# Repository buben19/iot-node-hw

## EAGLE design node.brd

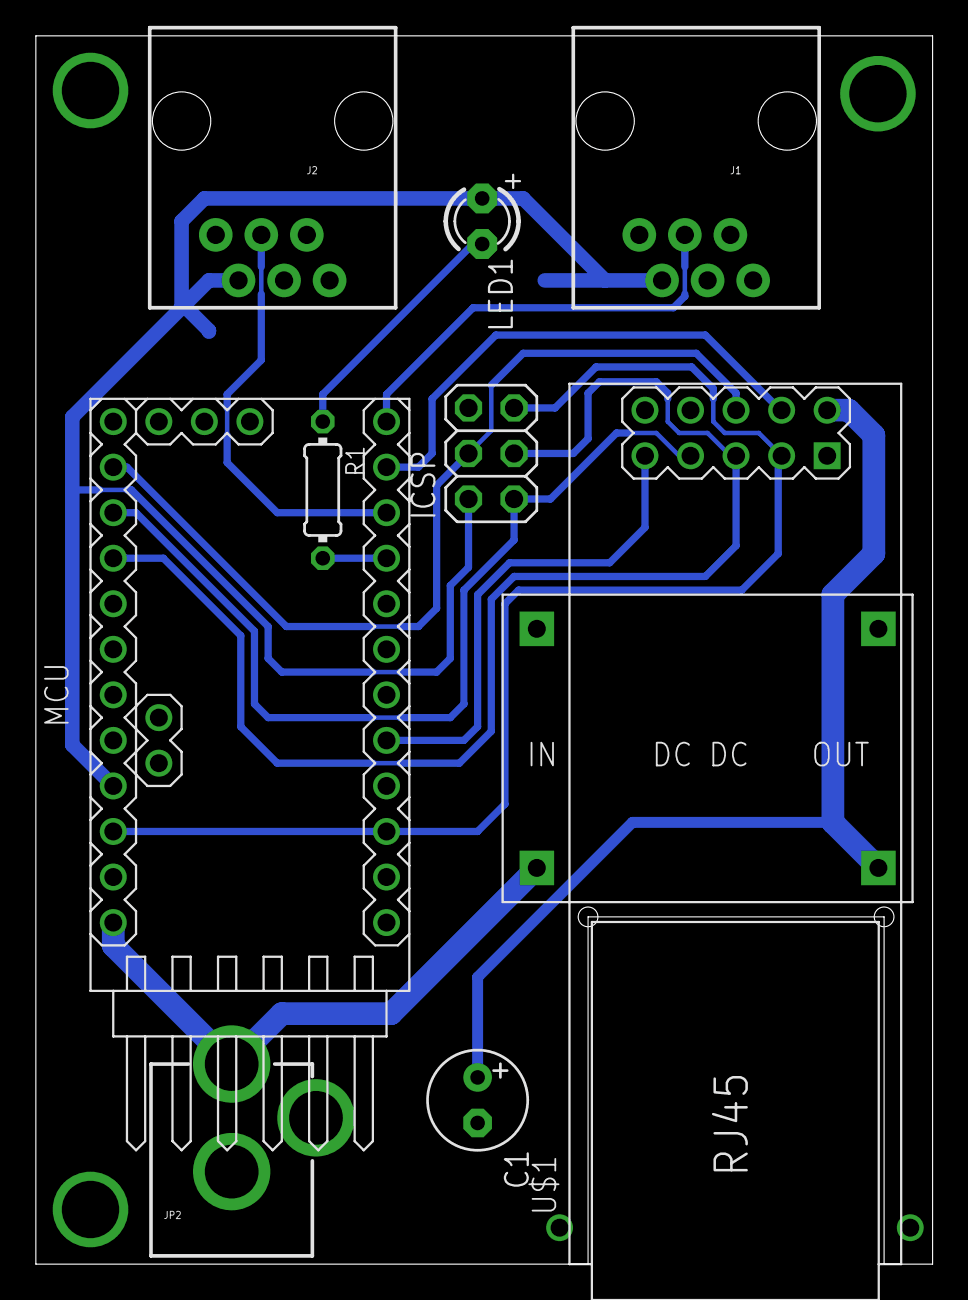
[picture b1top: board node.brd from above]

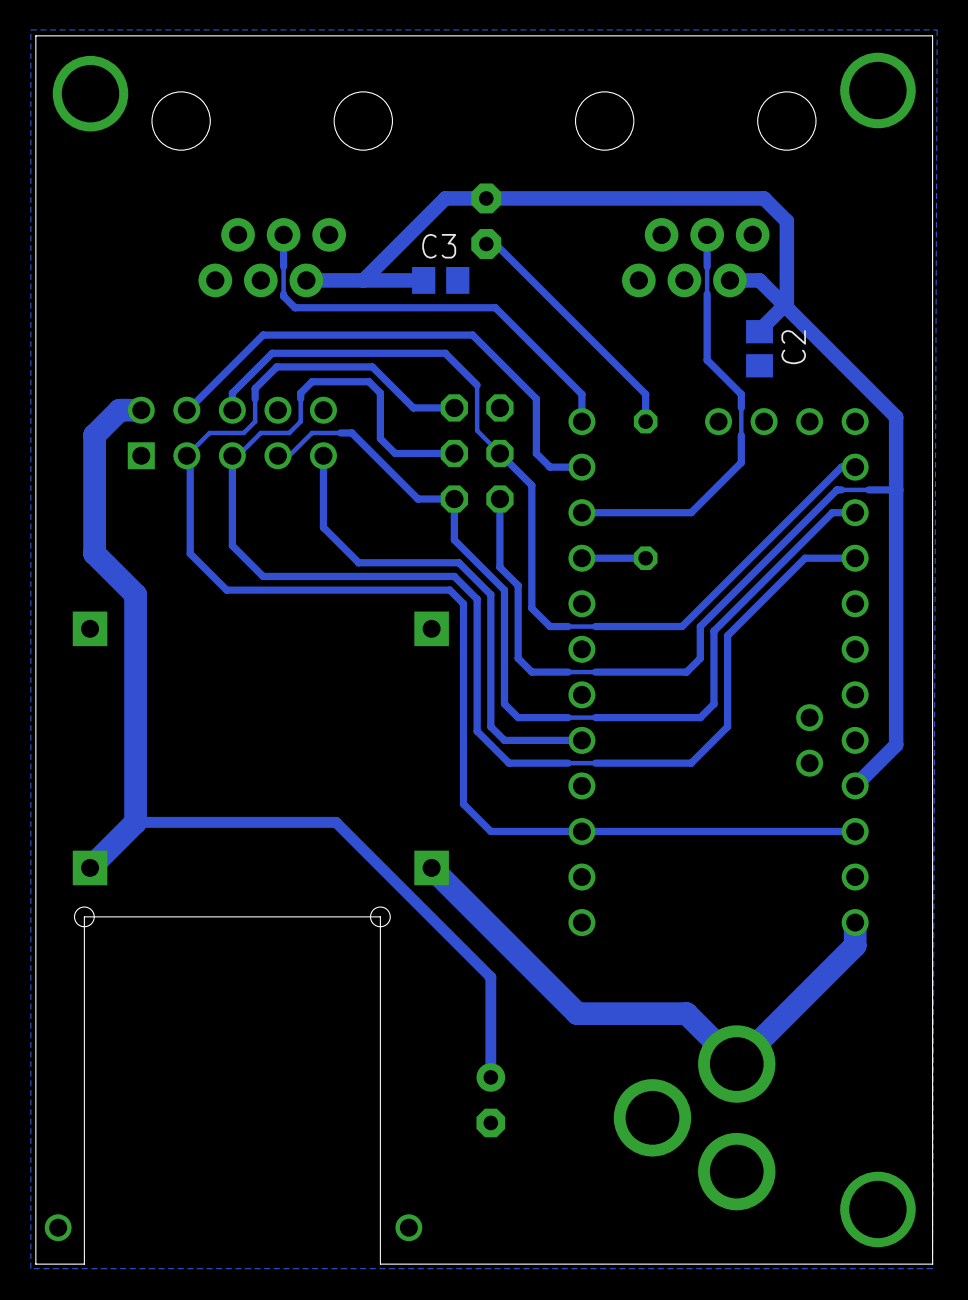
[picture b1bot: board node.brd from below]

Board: 2 copper layers, 50.0 x 68.5 mm, 12 parts (2 on the bottom side), 14 nets.

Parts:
C1: E2,5-6
C2, C3: 100nF; C0805
ICSP: 2X03
J1, J2: RJ11; RJ11-6
JP2: POWER_JACKPTH; POWER_JACK_PTH
LED1: LED3MM
MCU: ARDUINO-PRO-MINI-5.0V#APC; ARDUINO-PRO-MINI#APC
R1: 0204/7
U$1: ETHERNET-ENC28J60-MINI
U$2: DC-DC-SMALL; DC-DC

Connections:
+3V3: C1.+, U$1.VCC, U$2.P$2
+5V: C2.1, C3.1, ICSP.2, J1.5, J2.5, LED1.A, MCU.J6.4
DHT0_SIG: J1.4, MCU.J7.1
DHT1_SIG: J2.4, MCU.J7.3
ENC28J60_CS: MCU.J7.2, U$1.CS
ENC28J60_DATA_INT: MCU.J7.8, U$1.INT
GND: C1.-, C2.2, C3.2, ICSP.6, J1.2, J2.2, JP2.GND, JP2.GNDBREAK, MCU.J3.1, MCU.J6.2, MCU.J7.9, U$1.GND, U$2.P$3, U$2.P$4
LED_SINK: MCU.J7.4, R1.2
MISO: ICSP.1, MCU.J6.10, U$1.SO
MOSI: ICSP.4, MCU.J6.11, U$1.SI
unnamed: LED1.K, R1.1
RESET: ICSP.5, MCU.J6.3, MCU.J7.10, U$1.RST
SCK: ICSP.3, MCU.J6.9, U$1.SCK
VIN: JP2.PWR, MCU.J6.1, U$2.P$1

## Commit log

2015-11-06 Added 10k pull-up resistors.
2015-11-09 update epf file
2015-11-24 case: first commit
2015-11-24 Fixed case top part.
2016-01-11 New two layer board version (dirtypcbs.com).
2016-01-12 Minor fixes (verion number, signature, added some vias).
2016-01-12 Added gitignore file.
2016-01-12 Changed arduino footprint. Removed drills for unnecessary pins.

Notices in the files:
parts and their libraries:
diy-modules: Released under the Creative Commons Attribution 4.0 International License: http://creativecommons.org/licenses/by/4.0
SparkFun-Connectors: Licensing: Creative Commons ShareAlike 4.0 International - https://creativecommons.org/licenses/by-sa/4.0
